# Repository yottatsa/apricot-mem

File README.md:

# Apricot Xi Memory and IO Card 

Additional 640KB RAM, and IO breakout for prototyping.

Tested on PC/Xi, FP. Should be working on F2/F10. Not working on F1e with 128K RAM.

[Schematics](https://kicanvas.org/?github=https%3A%2F%2Fgithub.com%2Fyottatsa%2Fapricot-mem%2Fblob%2Fmain%2Fpcb%2Fapricot-mem.kicad_sch), 
[PCB](https://kicanvas.org/?github=https%3A%2F%2Fgithub.com%2Fyottatsa%2Fapricot-mem%2Fblob%2Fmain%2Fpcb%2Fapricot-mem.kicad_pcb), [Order from AISLER](https://aisler.net/p/DJKRDMKA)

## Building and flashing GAL

    make -C gal
    minipro -p ATF16V8C --write gal/xi.jed -P

## ToDo

* Loading caps on signal lines
* Move GAL to the left so it will be accessible without pulling the card
* Move testpoints to the bottom/make them THT, as it will make it more accessible from the case
* 3D-print a frame to hold the card in place
* DT/R̅ can be latched

## Board verification

- GAL is compilable and flash-able
- pins 12, 19 can not be used as input in registered mode

## Alternative options

* [Apricot F Series expandable SRAM board](https://github.com/stephen-usher/Apricot-RAM-Expansion) by S.R.Usher

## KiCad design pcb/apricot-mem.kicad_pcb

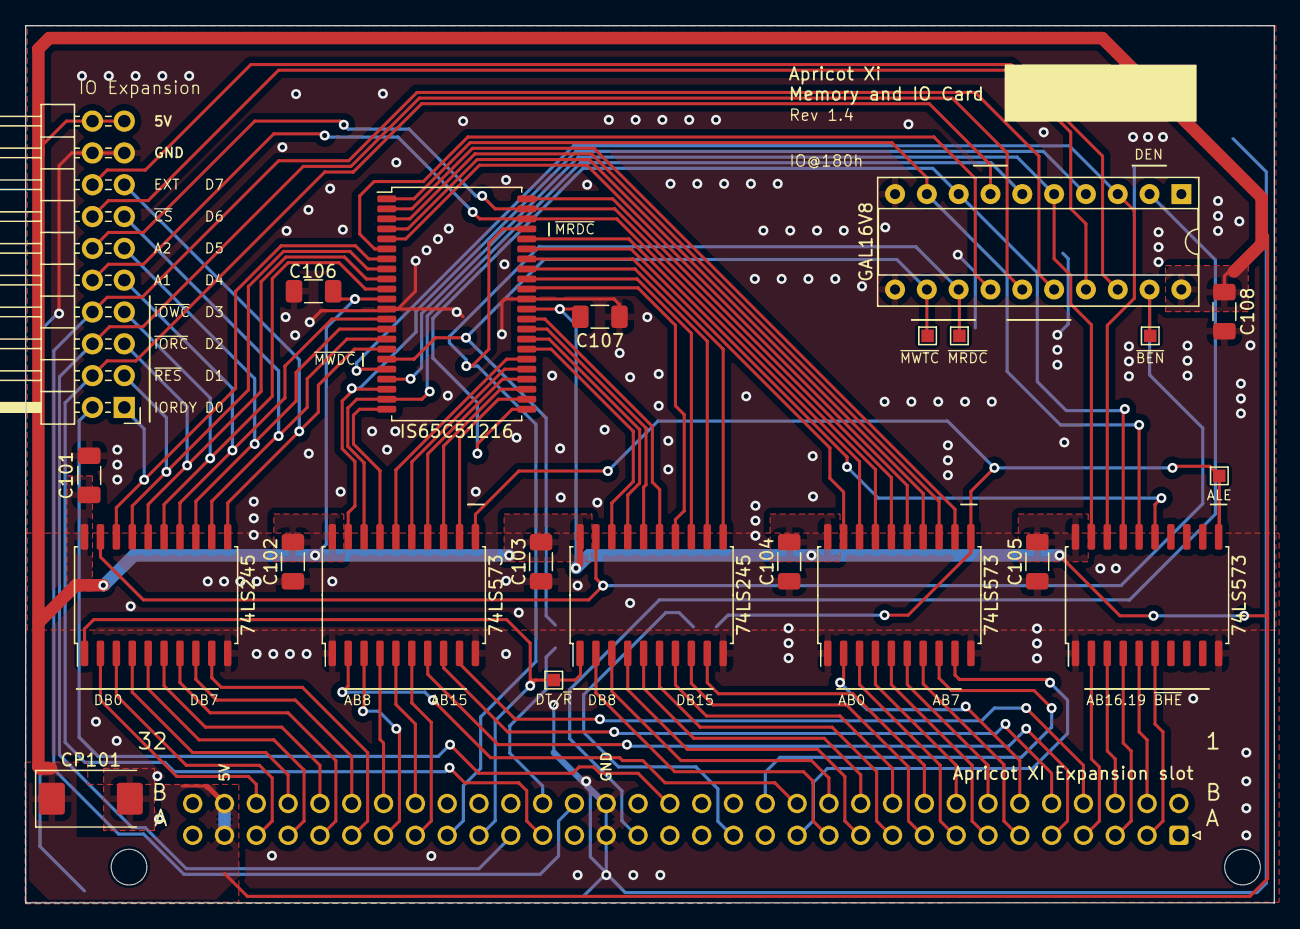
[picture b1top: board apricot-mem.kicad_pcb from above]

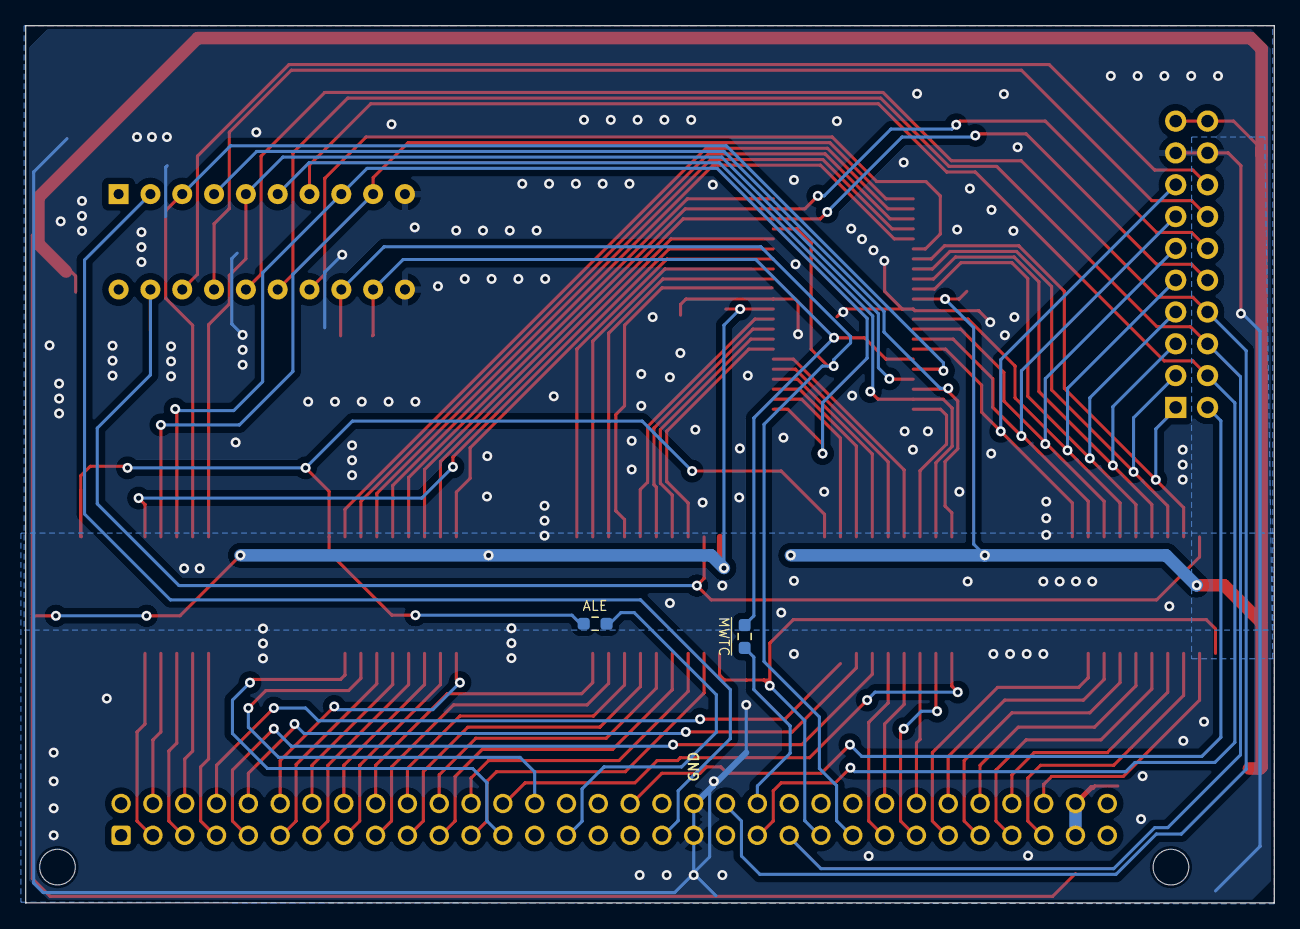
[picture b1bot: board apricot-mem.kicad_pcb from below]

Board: 2 copper layers, 99.7 x 70.0 mm, 25 parts (2 on the bottom side), 91 nets.

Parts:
C101, C102, C103, C104, C105, C106, C107, C108: 1uF PWR; C_1206_3216Metric_Pad1.33x1.80mm_HandSolder
CP101: PPWR; CP_EIA-7343-31_Kemet-D
J101: Apricot XI Expansion slot; DIN41612_B_2x32_Male_Horizontal_THT
J102: GAL16V8; DIP-20_W7.62mm_Socket
J103: IO Expansion; PinHeader_2x10_P2.54mm_Horizontal
R101: ~{MWTC}; R_0603_1608Metric_Pad0.98x0.95mm_HandSolder
R102: ALE; R_0603_1608Metric_Pad0.98x0.95mm_HandSolder
TP101: ALE; TestPoint_Pad_1.0x1.0mm
TP104: ~{MRDC}; TestPoint_Pad_1.0x1.0mm
TP105: ~{BEN}; TestPoint_Pad_1.0x1.0mm
TP106: DT/~{R}; TestPoint_Pad_1.0x1.0mm
TP107: ~{MWTC}; TestPoint_Pad_1.0x1.0mm
U101, U102, U103: 74LS573; SOIC-20W_7.5x12.8mm_P1.27mm
U104, U105: 74LS245; SOIC-20W_7.5x12.8mm_P1.27mm
U106: IS65C51216; TSOP-II-44_10.16x18.41mm_P0.8mm

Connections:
5VDC: C101.1, C102.1, C103.1, C104.1, C105.1, C106.1, C107.1, C108.1, CP101.1, J101.a31, J101.b31, J102.20 (VCC), J103.19, J103.20, U101.20 (VCC), U102.20 (VCC), U103.20 (VCC), U104.20 (VCC), U105.20 (VCC), U106.11 (VDD), U106.33 (VDD)
A0: U101.19 (Q0), U106.39 (~LB)
A1: J103.10, U101.18 (Q1), U106.42 (A7)
A2: J103.12, U101.17 (Q2), U106.43 (A6)
A3: U101.16 (Q3), U106.44 (A5)
A4: U101.15 (Q4), U106.5 (A0)
A5: U101.14 (Q5), U106.4 (A1)
A6: U101.13 (Q6), U106.3 (A2)
A7: U101.12 (Q7), U106.2 (A3)
A8: J102.4 (I4), U102.19 (Q0), U106.20 (A14)
A9: J102.6 (I6), U102.18 (Q1), U106.21 (A13)
A10: U102.17 (Q2), U106.22 (A12)
A11: U102.16 (Q3), U106.28 (A18)
A12: U102.15 (Q4), U106.27 (A8)
A13: U102.14 (Q5), U106.26 (A9)
A14: U102.13 (Q6), U106.25 (A10)
A15: U102.12 (Q7), U106.24 (A11)
A16: J102.5 (I5), U103.19 (Q0), U106.19 (A15)
A17: J102.3 (I3), U103.18 (Q1), U106.18 (A16)
A18: J102.8 (I8), U103.17 (Q2), U106.23 (A17)
A19: J102.9 (I9), U103.16 (Q3), U106.1 (A4)
AB0: J101.b6, U101.2 (D0)
AB1: J101.a8, U101.3 (D1)
AB2: J101.b8, U101.4 (D2)
AB3: J101.a7, U101.5 (D3)
AB4: J101.b7, U101.6 (D4)
AB5: J101.a6, U101.7 (D5)
AB6: J101.b14, U101.8 (D6)
AB7: J101.a13, U101.9 (D7)
AB8: J101.b13, U102.2 (D0)
AB9: J101.a26, U102.3 (D1)
AB10: J101.b26, U102.4 (D2)
AB11: J101.b25, U102.5 (D3)
AB12: J101.a25, U102.6 (D4)
AB13: J101.a5, U102.7 (D5)
AB14: J101.b5, U102.8 (D6)
AB15: J101.b4, U102.9 (D7)
AB16: J101.a4, U103.2 (D0)
AB17: J101.b3, U103.3 (D1)
AB18: J101.a3, U103.4 (D2)
AB19: J101.b2, U103.5 (D3)
ALE: R102.2, TP101.1, U101.11 (Load), U102.11 (Load), U103.11 (Load)
BUS.~ENABLED: J102.19 (IO1), TP105.1, U104.19 (CE), U105.19 (CE)
D0: J103.1, U104.18 (B0), U106.7 (DQ0)
D1: J103.3, U104.17 (B1), U106.8 (DQ1)
D2: J103.5, U104.16 (B2), U106.9 (DQ2)
D3: J103.7, U104.15 (B3), U106.10 (DQ3)
D4: J103.9, U104.14 (B4), U106.13 (DQ4)
D5: J103.11, U104.13 (B5), U106.14 (DQ5)
D6: J103.13, U104.12 (B6), U106.15 (DQ6)
D7: J103.15, U104.11 (B7), U106.16 (DQ7)
D8: U105.18 (B0), U106.29 (DQ8)
D9: U105.17 (B1), U106.30 (DQ9)
D10: U105.16 (B2), U106.31 (DQ10)
D11: U105.15 (B3), U106.32 (DQ11)
D12: U105.14 (B4), U106.35 (DQ12)
D13: U105.13 (B5), U106.36 (DQ13)
D14: U105.12 (B6), U106.37 (DQ14)
D15: U105.11 (B7), U106.38 (DQ15)
DB0: J101.b30, U104.2 (A0)
DB1: J101.a30, U104.3 (A1)
DB2: J101.b29, U104.4 (A2)
DB3: J101.a29, U104.5 (A3)
DB4: J101.b28, U104.6 (A4)
DB5: J101.a28, U104.7 (A5)
DB6: J101.b27, U104.8 (A6)
DB7: J101.a27, U104.9 (A7)
DB8: J101.a12, U105.2 (A0)
DB9: J101.b12, U105.3 (A1)
DB10: J101.a11, U105.4 (A2)
DB11: J101.b11, U105.5 (A3)
DB12: J101.a10, U105.6 (A4)
DB13: J101.b10, U105.7 (A5)
DB14: J101.a9, U105.8 (A6)
DB15: J101.b9, U105.9 (A7)
DEN: J101.a18, J102.2 (I2)
DT/~R: J101.a23, TP106.1, U104.1 (A->B), U105.1 (A->B)
EXP.SPARE: J102.18 (IO2), J103.16
EXP.~CS: J102.17 (I03), J103.14
GND: C101.2, C102.2, C103.2, C104.2, C105.2, C106.2, C107.2, C108.2, CP101.2, J101.a19, J101.b19, J102.10 (GND), J102.11 (I10/~OE), J103.17, J103.18, U101.1 (OE), U101.10 (GND), U102.1 (OE), U102.10 (GND), U103.1 (OE), U103.10 (GND), U104.10 (GND), U105.10 (GND), U106.12 (VSS), U106.34 (VSS)
IORDY: J101.b17, J103.2
MEM.~CS1: J102.14 (IO6), U106.6 (~CS1)
unnamed: J101.a15, R102.1
unnamed: J101.b21, R101.2
~BHE: J101.a2, U103.6 (D4)
~IORC: J101.a22, J102.15 (IO5), J103.6
~IOWC: J101.b20, J102.16 (IO4), J103.8
~MRDC: J101.a24, J102.13 (IO7), TP104.1, U106.41 (~OE)
~MWTC: J102.12 (IO8), R101.1, TP107.1, U106.17 (~WE)
~RES: J101.a21, J102.7 (I7), J103.4
~UB: U103.15 (Q4), U106.40 (~UB)

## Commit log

2023-04-18 initial
2023-04-19 fixing r1.3
2023-04-20 r1.3.2
2023-04-21 remove wrong fix
2023-04-21 r1.3.2 working revision
2023-04-22 docs
2023-04-26 +640KB
2023-04-26 artifacts
2023-10-28 Documentation for Apricot F1
2023-10-28 PCB Revision 1.4
    * better ground plane
    * link to AISLER
2023-10-29 gal makefile rework
2023-10-29 f1e 128K beta support
2023-11-01 readme
2023-11-01 removing unused formula
